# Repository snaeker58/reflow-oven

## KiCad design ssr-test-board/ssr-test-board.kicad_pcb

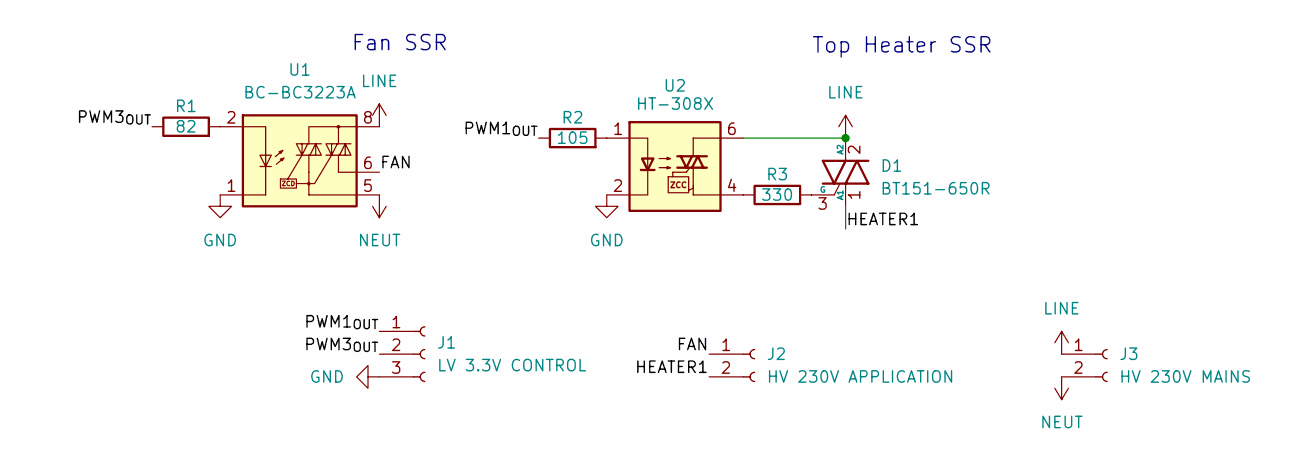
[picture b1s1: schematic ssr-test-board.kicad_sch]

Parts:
D1: BT151-650R; TO-220-3_Vertical; LCSC-Part C2831674
J1: LV 3.3V CONTROL; PinHeader_1x03_P2.54mm_Vertical
J2: HV 230V APPLICATION; PinHeader_1x02_P2.54mm_Vertical
J3: HV 230V MAINS; PinHeader_1x02_P2.54mm_Vertical
R1: 82; R_0603_1608Metric_Pad0.98x0.95mm_HandSolder; LCSC-Part C3017760
R2: 105; R_0603_1608Metric_Pad0.98x0.95mm_HandSolder; LCSC-Part C3016240
R3: 330; R_0603_1608Metric_Pad0.98x0.95mm_HandSolder; LCSC-Part C2907152
U1: BC-BC3223A; SSO-7-8_6.4x9.78mm_P2.54mm; LCSC-Part C596515
U2: HT-308X; DIP-6_W7.62mm; LCSC-Part C34376216

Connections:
/FAN: J2.1, U1.6
/HEATER1: D1.1 (A1), J2.2
/PWM1_{OUT}: J1.1, R2.1
/PWM3_{OUT}: J1.2, R1.1
GND: J1.3, U1.1, U1.3, U1.4, U2.2
LINE: D1.2 (A2), J3.1, U1.8, U2.6
NEUT: J3.2, U1.5
unnamed: D1.3 (G), R3.2
unnamed: R1.2, U1.2
unnamed: R2.2, U2.1
unnamed: R3.1, U2.4

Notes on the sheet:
Fan SSR
Top Heater SSR

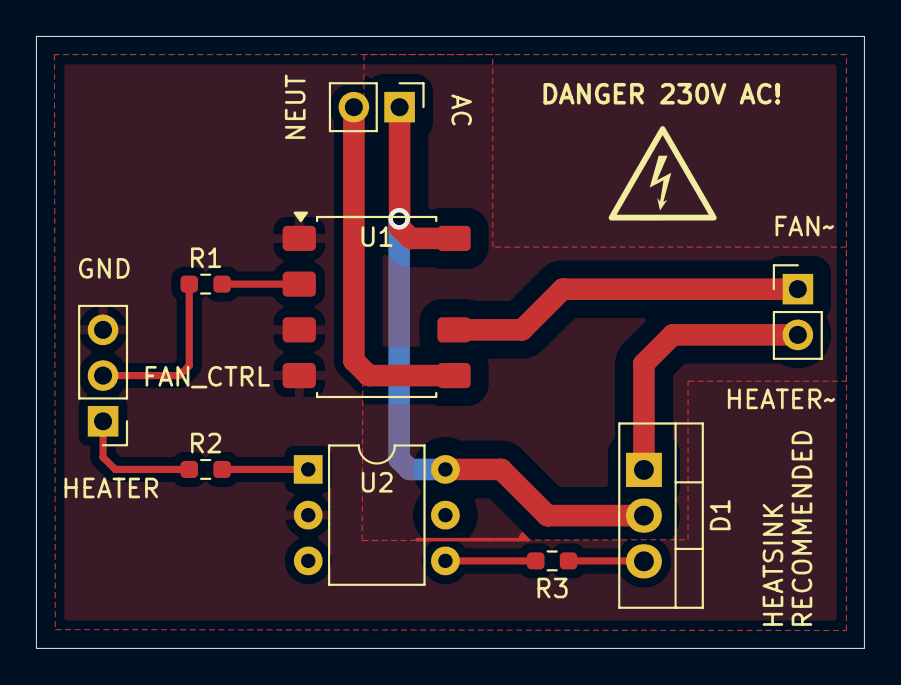
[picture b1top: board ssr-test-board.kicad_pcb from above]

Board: 2 copper layers, 46.0 x 34.0 mm, 9 parts (0 on the bottom side), 11 nets.

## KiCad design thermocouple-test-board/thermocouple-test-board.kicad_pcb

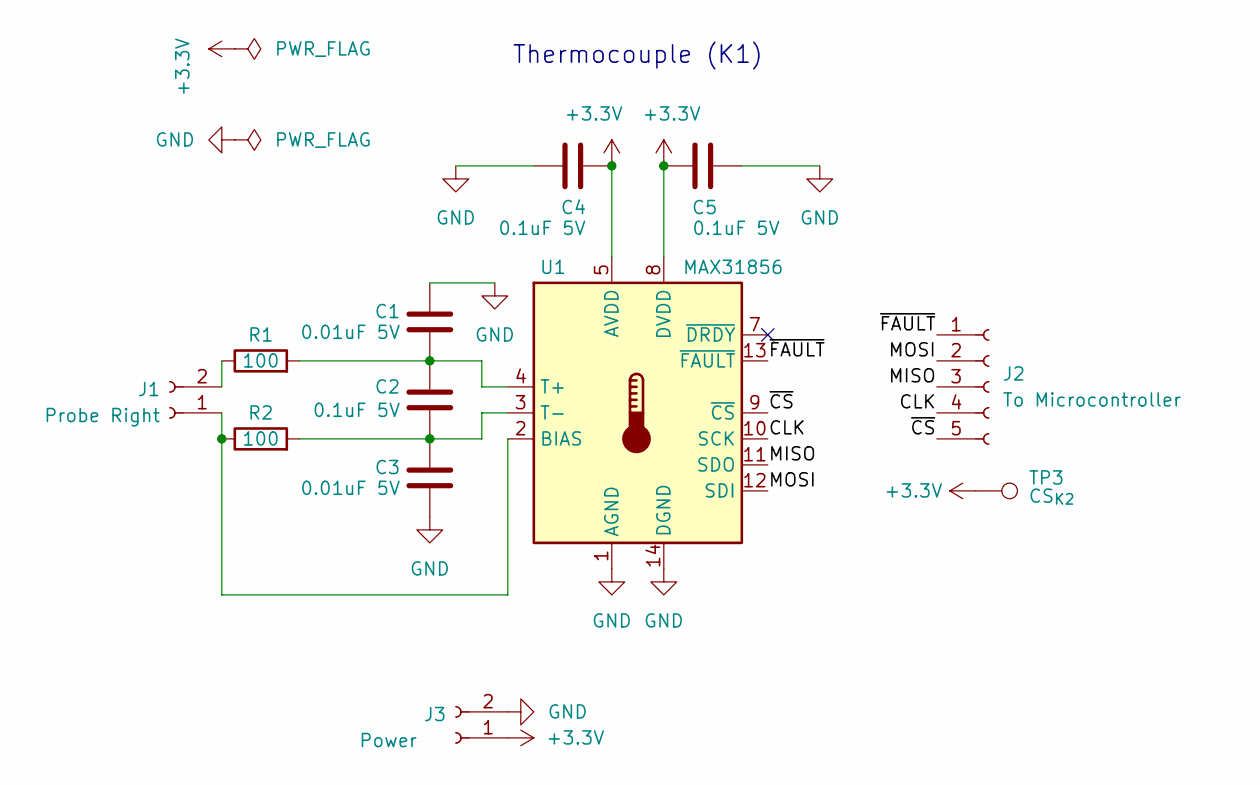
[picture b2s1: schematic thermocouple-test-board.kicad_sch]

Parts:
C1, C3: 0.01uF 5V; C_0603_1608Metric_Pad1.08x0.95mm_HandSolder; LCSC-Part C376807
C2, C4, C5: 0.1uF 5V; C_0603_1608Metric_Pad1.08x0.95mm_HandSolder; LCSC-Part C5137636
J1: Probe Right; PinSocket_1x02_P2.54mm_Vertical; LCSC-Part C5179471
J2: To Microcontroller; PinSocket_1x05_P2.54mm_Vertical
J3: Power; PinSocket_1x02_P2.54mm_Vertical; LCSC-Part C5179471
R1, R2: 100; R_0603_1608Metric_Pad0.98x0.95mm_HandSolder; LCSC-Part C3017758
TP3: CS_{K2}; TestPoint_Pad_D2.5mm
U1: MAX31856; TSSOP-14_4.4x5mm_P0.65mm; LCSC-Part C2653162

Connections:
+3.3V: C4.1, C5.1, J3.1, TP3.1, U1.5 (AVDD), U1.8 (DVDD)
/CLK: J2.4, U1.10 (SCK)
/MISO: J2.3, U1.11 (SDO)
/MOSI: J2.2, U1.12 (SDI)
/~CS: J2.5, U1.9 (~CS)
/~FAULT: J2.1, U1.13 (~FAULT)
GND: C1.2, C3.2, C4.2, C5.2, J3.2, U1.1 (AGND), U1.14 (DGND)
unnamed: J1.1, R2.1, U1.2 (BIAS)
unnamed: J1.2, R1.1
unnamed: C1.1, C2.1, R1.2, U1.4 (T+)
unnamed: C2.2, C3.1, R2.2, U1.3 (T-)

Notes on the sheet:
Thermocouple (K1)

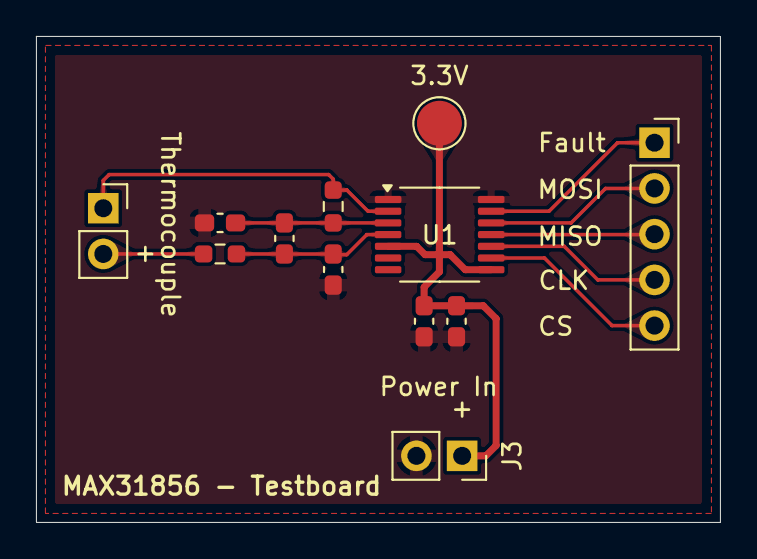
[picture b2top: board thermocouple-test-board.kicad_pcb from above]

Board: 2 copper layers, 38.0 x 27.0 mm, 12 parts (0 on the bottom side), 11 nets.

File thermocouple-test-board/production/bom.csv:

Designator,Footprint,Quantity,Value,LCSC Part #
"C1, C3",0603,2,0.01uF 5V,
"C2, C4, C5",0603,3,0.1uF 5V,
J1,PinSocket_1x02_P2.54mm_Vertical,1,Probe Right,
J2,PinSocket_1x05_P2.54mm_Vertical,1,To Microcontroller,
J3,PinSocket_1x02_P2.54mm_Vertical,1,Power,
"R1, R2",0603,2,100,
TP3,TestPoint_Pad_D2.5mm,1,CS_{K2},
U1,TSSOP-14_4.4x5mm_P0.65mm,1,MAX31856,

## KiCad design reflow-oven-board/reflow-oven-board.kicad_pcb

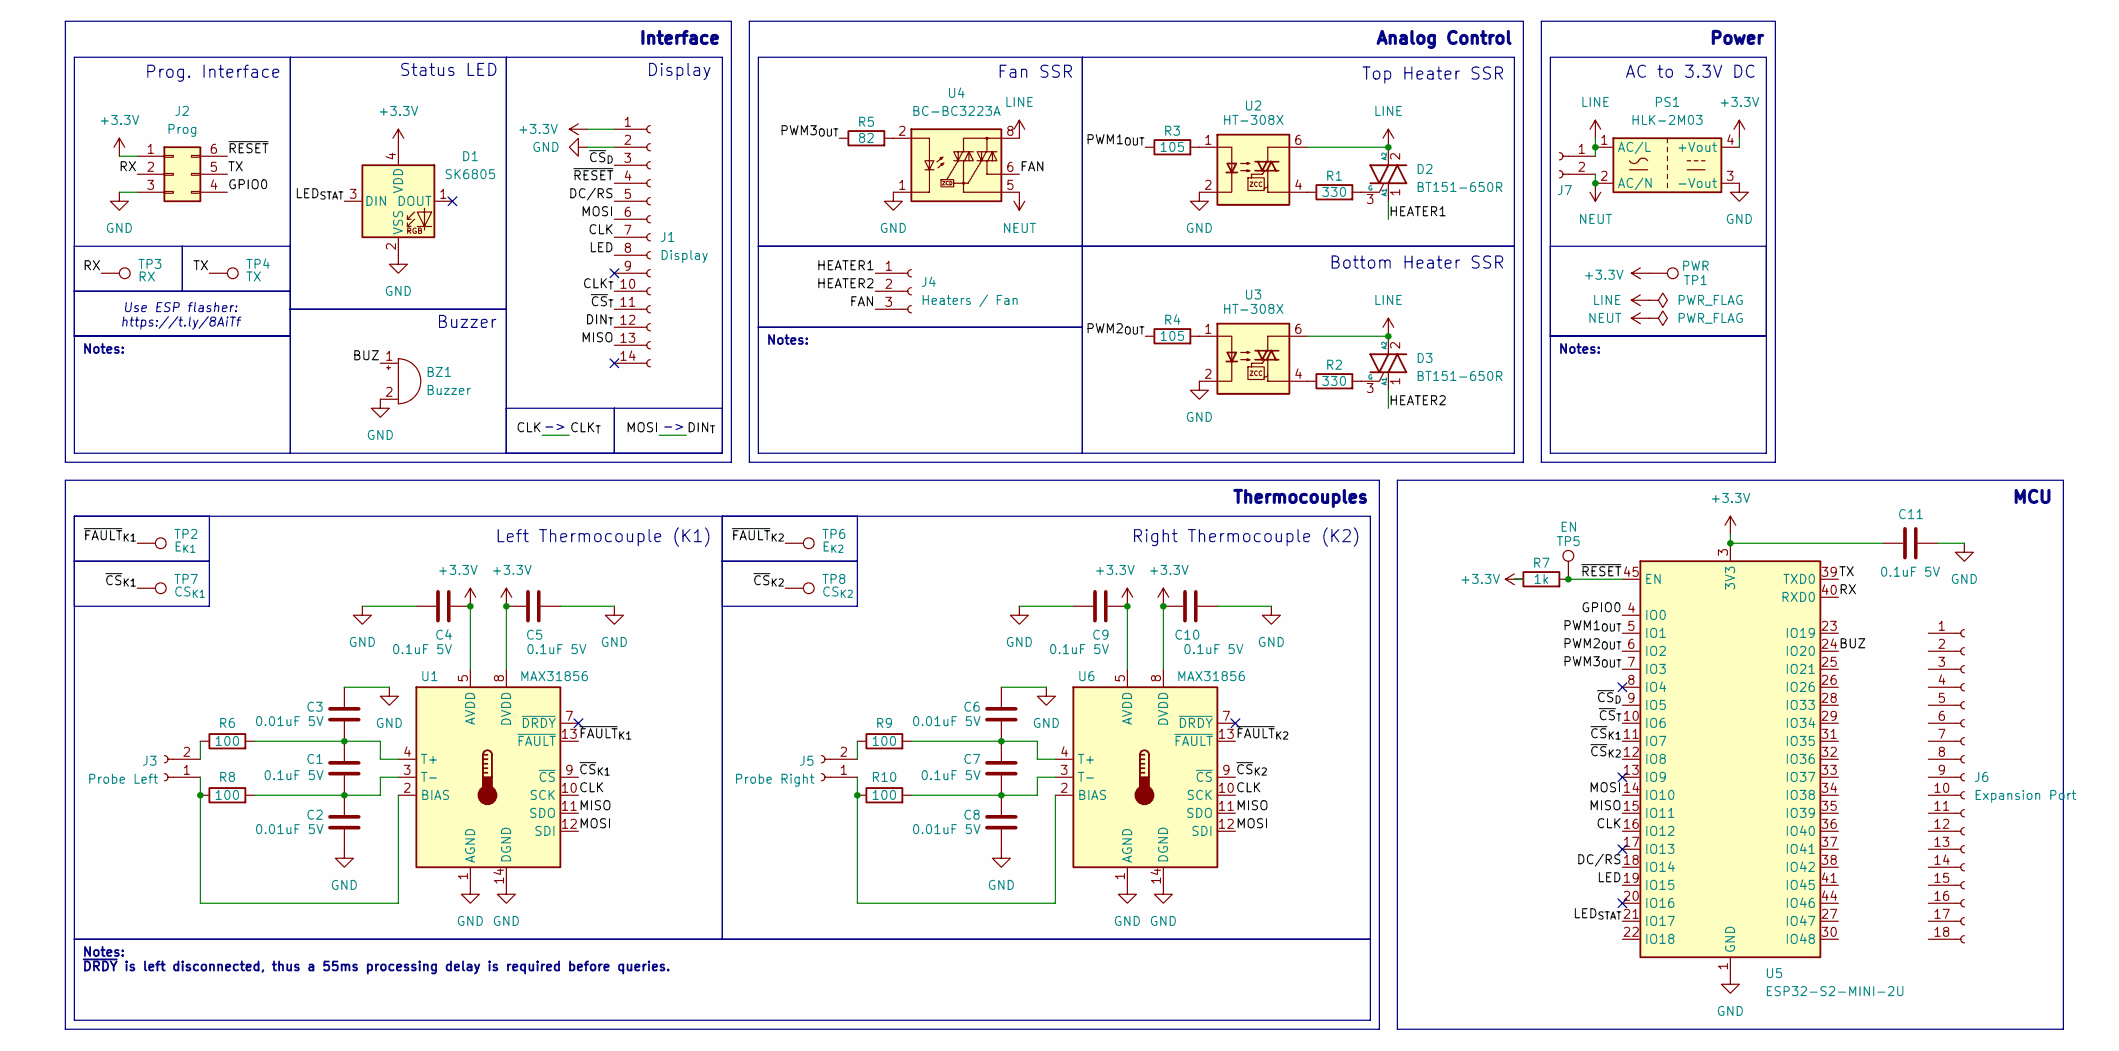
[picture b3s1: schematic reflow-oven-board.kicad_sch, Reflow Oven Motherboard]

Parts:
BZ1: Buzzer; MagneticBuzzer_PUI_AT-0927-TT-6-R; LCSC-Part C96256
C1, C4, C5, C7, C9, C10, C11: 0.1uF 5V; C_0603_1608Metric_Pad1.08x0.95mm_HandSolder; LCSC-Part C5137636
C2, C3, C6, C8: 0.01uF 5V; C_0603_1608Metric_Pad1.08x0.95mm_HandSolder; LCSC-Part C376807
D1: SK6805; LED_SK6805_PLCC4_2.4x2.7mm_P1.3mm; LCSC-Part C2909056
D2, D3: BT151-650R; TO-220-3_Vertical; LCSC-Part C2831674
J1: Display; EA_eDIPTFT-HR4-9668S01
J2: Prog; PinHeader_2x03_P1.27mm_Vertical
J3: Probe Left; DORABO DBT50G-6.35-2P-BK-P OGC; LCSC-Part C5179471
J4: Heaters / Fan; DORABO DBT50G-6.35-3P-BK-P OGC; LCSC-Part C5179472
J5: Probe Right; DORABO DBT50G-6.35-2P-BK-P OGC; LCSC-Part C5179471
J6: Expansion Port; PinHeader_1x18_P1.27mm_Vertical
J7: Power In; DORABO DBT50G-6.35-2P-BK-P OGC; LCSC-Part C5179471
PS1: HLK-2M03; Converter_ACDC_Hi-Link_HLK-2Mxx; LCSC-Part C399249
R1, R2: 330; R_0603_1608Metric_Pad0.98x0.95mm_HandSolder; LCSC-Part C2907152
R3, R4: 105; R_0603_1608Metric_Pad0.98x0.95mm_HandSolder; LCSC-Part C3016240
R5: 82; R_0603_1608Metric_Pad0.98x0.95mm_HandSolder; LCSC-Part C3017760
R6, R8, R9, R10: 100; R_0603_1608Metric_Pad0.98x0.95mm_HandSolder; LCSC-Part C3017758
R7: 1k; R_0603_1608Metric_Pad0.98x0.95mm_HandSolder; LCSC-Part C328340
TP1: PWR; TestPoint_Pad_D1.5mm
TP2: E_{K1}; TestPoint_Pad_D1.5mm
TP3: RX; TestPoint_Pad_D1.5mm
TP4: TX; TestPoint_Pad_D1.5mm
TP5: EN; TestPoint_Pad_D1.5mm
TP6: E_{K2}; TestPoint_Pad_D1.5mm
TP7: CS_{K1}; TestPoint_Pad_D1.5mm
TP8: CS_{K2}; TestPoint_Pad_D1.5mm
U1, U6: MAX31856; TSSOP-14_4.4x5mm_P0.65mm; LCSC-Part C2653162
U2, U3: HT-308X; DIP-6_W7.62mm; LCSC-Part C34376216
U4: BC-BC3223A; SSO-7-8_6.4x9.78mm_P2.54mm; LCSC-Part C596515
U5: ESP32-S2-MINI-2U; ESP32-S2-MINI-1U; LCSC-Part C3013909

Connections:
+3.3V: C4.1, C5.1, C9.1, C10.1, C11.1, D1.4 (VDD), J1.1, J2.1, PS1.4 (+Vout), R7.1, TP1.1, U1.5 (AVDD), U1.8 (DVDD), U5.3 (3V3), U6.5 (AVDD), U6.8 (DVDD)
/BUZ: BZ1.1 (+), U5.24 (IO20)
/CLK: J1.7, J1.10, U1.10 (SCK), U5.16 (IO12), U6.10 (SCK)
/DC/RS: J1.5, U5.18 (IO14)
/DIN_{T}: J1.6, J1.12, U1.12 (SDI), U5.14 (IO10), U6.12 (SDI)
/FAN: J4.3, U4.6
/GPIO0: J2.4, U5.4 (IO0)
/HEATER1: D2.1 (A1), J4.1
/HEATER2: D3.1 (A1), J4.2
/LED: J1.8, U5.19 (IO15)
/LED_{STAT}: D1.3 (DIN), U5.21 (IO17)
/MISO: J1.13, U1.11 (SDO), U5.15 (IO11), U6.11 (SDO)
/PWM1_{OUT}: R3.1, U5.5 (IO1)
/PWM2_{OUT}: R4.1, U5.6 (IO2)
/PWM3_{OUT}: R5.1, U5.7 (IO3)
/RX: J2.2, TP3.1, U5.40 (RXD0)
/TX: J2.5, TP4.1, U5.39 (TXD0)
/~CS_{D}: J1.3, U5.9 (IO5)
/~CS_{K1}: TP7.1, U1.9 (~CS), U5.11 (IO7); also elsewhere on the board
/~CS_{K2}: TP8.1, U5.12 (IO8), U6.9 (~CS); also elsewhere on the board
/~CS_{T}: J1.11, U5.10 (IO6)
/~FAULT_{K1}: TP2.1, U1.13 (~FAULT); also elsewhere on the board
/~FAULT_{K2}: TP6.1, U6.13 (~FAULT); also elsewhere on the board
/~RESET: J1.4, J2.6, R7.2, TP5.1, U5.45 (EN)
GND: BZ1.2 (-), C2.2, C3.2, C4.2, C5.2, C6.2, C8.2, C9.2, C10.2, C11.2, D1.2 (VSS), J1.2, J2.3, PS1.3 (-Vout), U1.1 (AGND), U1.14 (DGND), U2.2, U3.2, U4.1, U4.3, U4.4, U5.1 (GND), U5.2 (GND), U5.42 (GND), U5.43 (GND), U5.46 (GND), U5.47 (GND), U5.48 (GND), U5.49 (GND), U5.50 (GND), U5.51 (GND), U5.52 (GND), U5.53 (GND), U5.54 (GND), U5.55 (GND), U5.56 (GND), U5.57 (GND), U5.58 (GND), U5.59 (GND), U5.60 (GND), U5.61 (GND), U5.62 (GND), U5.63 (GND), U5.64 (GND), U5.65 (GND), U6.1 (AGND), U6.14 (DGND)
LINE: D2.2 (A2), D3.2 (A2), J7.1, PS1.1 (AC/L), U2.6, U3.6, U4.8
NEUT: J7.2, PS1.2 (AC/N), U4.5
unnamed: D2.3 (G), R1.2
unnamed: D3.3 (G), R2.2
unnamed: J3.1, R8.1, U1.2 (BIAS)
unnamed: J3.2, R6.1
unnamed: J5.1, R10.1, U6.2 (BIAS)
unnamed: J5.2, R9.1
unnamed: R1.1, U2.4
unnamed: R2.1, U3.4
unnamed: R3.2, U2.1
unnamed: R4.2, U3.1
unnamed: R5.2, U4.2
unnamed: C1.1, C3.1, R6.2, U1.4 (T+)
unnamed: C1.2, C2.1, R8.2, U1.3 (T-)
unnamed: C6.1, C7.1, R9.2, U6.4 (T+)
unnamed: C7.2, C8.1, R10.2, U6.3 (T-)

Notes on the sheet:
Thermocouples
Analog Control
Power
Notes:
Interface
MCU
Notes: ~{DRDY} is left disconnected, thus a 55ms processing delay is required before queries.
Prog. Interface
Bottom Heater SSR
Top Heater SSR
Display
Buzzer
Use ESP flasher: https://t.ly/8AiTf
Left Thermocouple (K1)
AC to 3.3V DC
Right Thermocouple (K2)
Fan SSR
Status LED

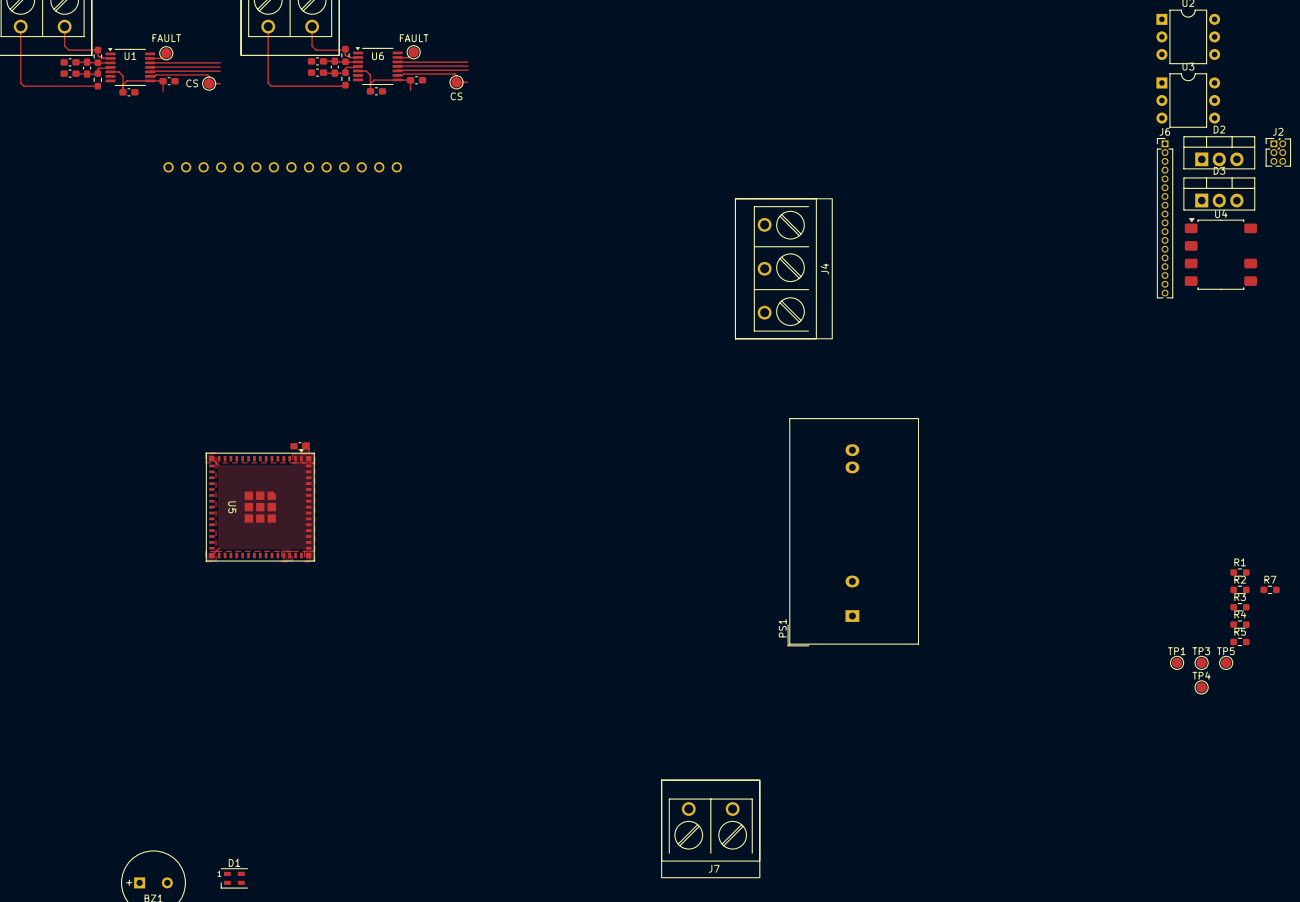
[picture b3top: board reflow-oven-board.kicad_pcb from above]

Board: 2 copper layers, 47 parts (1 on the bottom side), 42 nets.

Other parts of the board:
CS: CS_{K1}; TestPoint_Pad_D1.5mm
CS#2: CS_{K2}; TestPoint_Pad_D1.5mm
FAULT: E_{K1}; TestPoint_Pad_D1.5mm
FAULT#2: E_{K2}; TestPoint_Pad_D1.5mm

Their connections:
/~CS_{K1}: CS.1; also elsewhere on the board
/~CS_{K2}: CS#2.1; also elsewhere on the board
/~FAULT_{K1}: FAULT.1; also elsewhere on the board
/~FAULT_{K2}: FAULT#2.1; also elsewhere on the board

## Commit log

2024-10-16 Reset Project
2024-10-16 Fully reset
2024-11-18 Added firmware prototype
2024-11-26 Added Test Boards
2024-11-26 Progress Bar Test
2024-11-26 Fixed typo
2024-11-27 Resync
